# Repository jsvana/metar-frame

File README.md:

# metar

Arduino sketch to light up some LEDs on a sectional.

Fun side project. Probably does things wrong, and isn't really useful unless you have the same setup I do. Feel free to use as a reference if you want!

## TODO
- Picture
- KiCAD schematic

## License

[MIT](LICENSE.md)

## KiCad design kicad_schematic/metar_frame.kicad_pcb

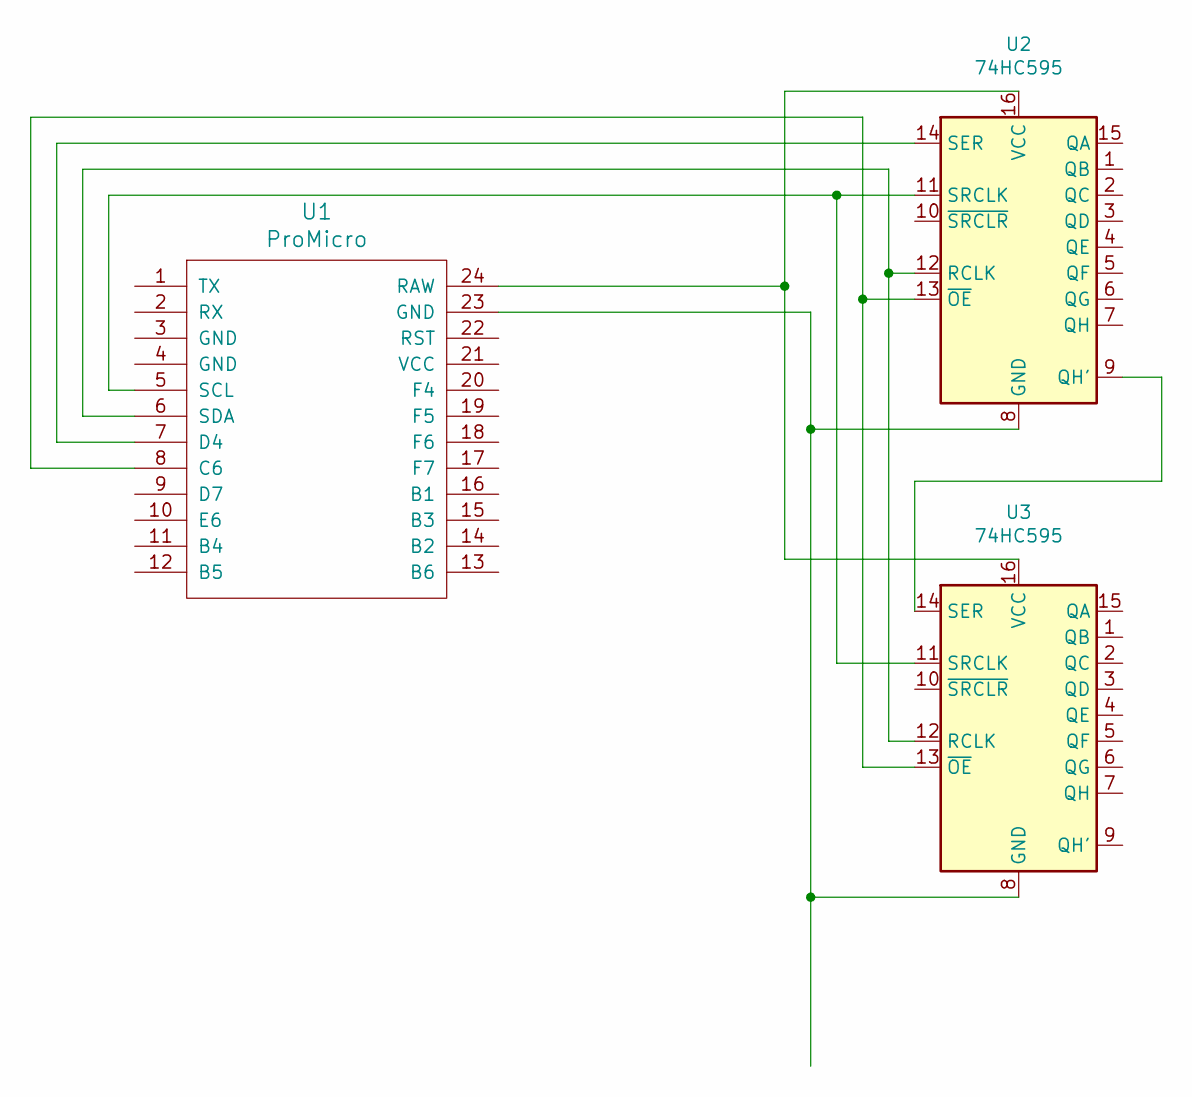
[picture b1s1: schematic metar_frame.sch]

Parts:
U1: ProMicro
U2, U3: 74HC595; DIP-16_W7.62mm_Socket

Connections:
unnamed: U1.23 (GND), U2.8 (GND), U3.8 (GND)
unnamed: U1.5 (SCL), U2.11 (SRCLK), U3.11 (SRCLK)
unnamed: U1.6 (SDA), U2.12 (RCLK), U3.12 (RCLK)
unnamed: U1.7 (D4), U2.14 (SER)
unnamed: U1.8 (C6), U2.13 (~OE), U3.13 (~OE)
unnamed: U1.24 (RAW), U2.16 (VCC), U3.16 (VCC)
unnamed: U2.9 (QH'), U3.14 (SER)

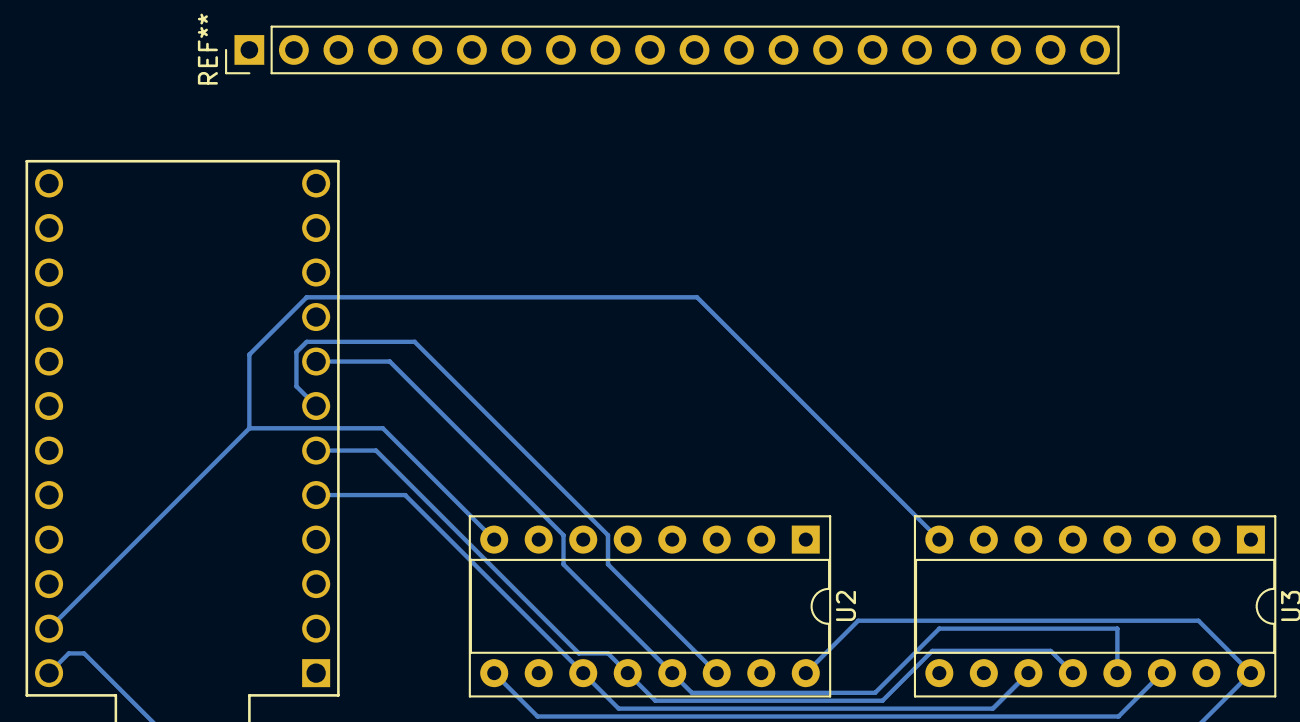
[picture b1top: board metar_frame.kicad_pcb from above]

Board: 2 copper layers, 3 parts (0 on the bottom side), 7 nets.

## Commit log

2021-02-20 Use iterators
2021-02-20 Add readme and license
2021-02-23 Start work on schematic
